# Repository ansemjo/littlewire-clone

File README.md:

# littlewire-clone

This is a clone of [Little Wire](https://littlewire.github.io/) by Ihsan Kehribar
with mostly SMD parts.

The special part about it is that it uses a female ICSP header soldered
on the edge of the board, which can be plugged into the target device
directly or used with "pogo-pin" adapters like
[the one by Pnoxi](https://www.tindie.com/products/pnoxi/avr-isp-pogo-pin-adapter-2x3-idc2x3-pogo-254mm/).

*Yes, I know my C2 is crooked .. Next time I'll use the "elongated pads" footprint.*

## Project structure

There's a number of interesting subdirectories, in order of applicability:

| Directory | Description |
| --------- | ----------- |
| [`hardware`](hardware/) | The KiCad 5.1.6 project with schematics and manufacturing files for PCB production. |
| [`bootloader`](bootloader/) | Instructions on how to put the `micronucleus` bootloader onto the chip once it's assembled. |
| [`firmware`](firmware/) | A vendored copy of the Little Wire / `usbtiny` source code to install the firmware.

## First batch

I have ordered the first batch thorugh [aisler.net](https://aisler.net/). From those
I have now assembled and tested two boards.

Currently I have **6** circuit boards left. Shoot me a
[message](https://twitter.com/ansemjo) if you want one of those.

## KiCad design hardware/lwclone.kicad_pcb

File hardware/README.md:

# Little Wire Clone

This directory describes a KiCad 5.1.6 project directory for my clone of
the Little Wire project by Ihsan Kehribar.

## Bill of Materials

Here is an informal BOM with the parts I used for my two boards so far.
Note that some of the values don't match with the schematic; I used some parts
that I had available from previous orders where it shouldn't make too much of
a difference anyway.

| ref | amount | partno | name |
| --- | ------ | ------ | ---- |
| U1 | 1 | ATTINY85-20PU | Microchip Technology ATTINY85-20PU IC MCU 8BIT 8KB FLASH 8DIP |
| USB1 | 1 | 10118194-0001LF | Amphenol ICC CONN RCPT USB2.0 MICRO B SMD R/A |
| C1, C2 | 2 | CL21B104KACNNNC | Samsung CAP CER 0.1UF 25V X7R 0805 |
| D1, D2 | 2 | MMSZ4684T1G | ON Semiconductor DIODE ZENER 3.3V 500MW SOD123 |
| D3 | 1 | LTST-C171AKT | Lite-On Inc. LED ORANGE CLEAR SMD |
| R1, R2 | 2 | RC0805FR-07100RL | Yageo RES SMD 100 OHM 1% 1/8W 0805 |
| R3 | 1 | RC0805FR-072K2L | Yageo RES SMD 2.2K OHM 1% 1/8W 0805 |
| R4 | 1 | RC0805FR-07330RL | Yageo RES SMD 330 OHM 1% 1/8W 0805 |
| ICSP1 | 1 | SSQ-103-01-T-D | Samtec Inc. CONN RCPT 6POS 0.1 TIN PCB |

## LICENSE

Copyright (c) 2020 Anton Semjonov

This source describes Open Hardware and is licensed under the CERN-OHL-P v2

You may redistribute and modify this documentation and make products using it
under the terms of the CERN-OHL-P v2 (https:/cern.ch/cern-ohl). This
documentation is distributed WITHOUT ANY EXPRESS OR IMPLIED WARRANTY, INCLUDING
OF MERCHANTABILITY, SATISFACTORY QUALITY AND FITNESS FOR A PARTICULAR PURPOSE.
Please see the CERN-OHL-P v2 for applicable conditions.

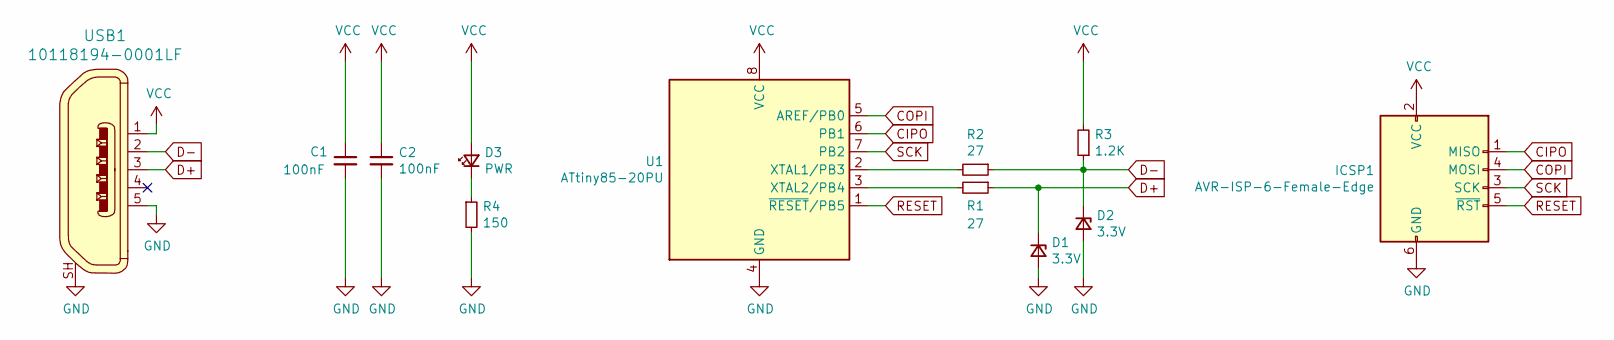
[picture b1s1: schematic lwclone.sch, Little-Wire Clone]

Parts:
C1, C2: 100nF; C_0805_2012Metric
D1, D2: 3.3V; D_SOD-123
D3: PWR; LED_0805_2012Metric
ICSP1: AVR-ISP-6-Female-Edge; IDC-Edge-Header-Female_2x03_P2.54mm
R1, R2: 27; R_0805_2012Metric
R3: 1.2K; R_0805_2012Metric
R4: 150; R_0805_2012Metric
U1: ATtiny85-20PU; DIP-8_W7.62mm
USB1: 10118194-0001LF; USB_Micro_B_Female_10118194-0001LF; MPN 10118194-0001LF; Digi-Key_PN 609-4618-1-ND

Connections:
CIPO: ICSP1.1 (MISO), U1.6 (PB1)
COPI: ICSP1.4 (MOSI), U1.5 (AREF/PB0)
D+: D1.1 (K), R1.1, USB1.3
D-: D2.1 (K), R2.1, R3.1, USB1.2
GND: C1.2, C2.2, D1.2 (A), D2.2 (A), ICSP1.6 (GND), R4.2, U1.4 (GND), USB1.5, USB1.SH
unnamed: D3.1 (K), R4.1
unnamed: R1.2, U1.3 (XTAL2/PB4)
unnamed: R2.2, U1.2 (XTAL1/PB3)
RESET: ICSP1.5 (~RST), U1.1 (~RESET~/PB5)
SCK: ICSP1.3 (SCK), U1.7 (PB2)
VCC: C1.1, C2.1, D3.2 (A), ICSP1.2 (VCC), R3.2, U1.8 (VCC), USB1.1

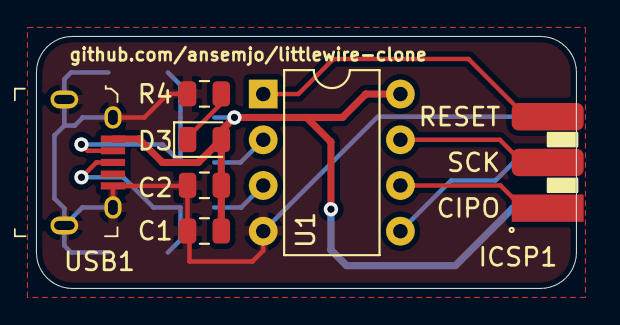
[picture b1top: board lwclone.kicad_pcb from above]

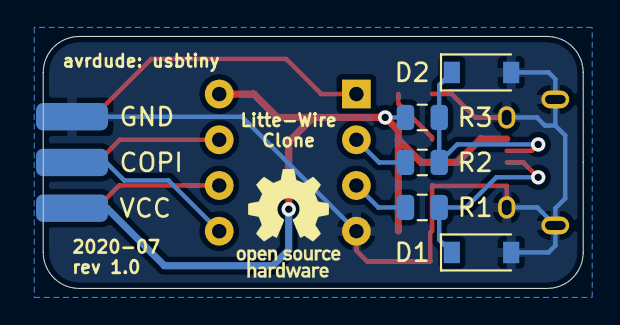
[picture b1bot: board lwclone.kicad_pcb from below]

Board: 2 copper layers, 30.0 x 14.0 mm, 12 parts (5 on the bottom side), 11 nets.

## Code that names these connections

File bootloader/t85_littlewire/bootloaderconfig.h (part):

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 * 
 * Controller type: ATtiny 85 - 16.5 MHz
 * Configuration:   Default configuration
 *       USB D- :   PB3
 *       USB D+ :   PB4
 *       Entry  :   Always
 *       LED    :   None
 *       OSCCAL :   Stays at 16 MHz
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 *                      external jumper. 
 *                      Adds 34 bytes.
 *
 *       JUMPER_PIN     Pin the jumper is connected to. (e.g. PB0)
 *       JUMPER_PORT    Port out register for the jumper (e.g. PORTB)  
 *       JUMPER_DDR     Port data direction register for the jumper (e.g. DDRB)  
 *       JUMPER_INP     Port inout register for the jumper (e.g. PINB)  
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
#define ENTRYMODE ENTRY_JUMPER

#define JUMPER_PIN    PB5
#define JUMPER_PORT   PORTB 
#define JUMPER_DDR    DDRB 
#define JUMPER_INP    PINB 
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
#define LED_DDR     DDRB
#define LED_PORT    PORTB
#define LED_PIN     PB1

/*
 *  This is the implementation of the LED code. Change the configuration above unless you want to 
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
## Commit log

2020-07-04 commit first revision ordered on aisler.net
2020-07-04 copy all used symbols to local lwclone.lib
2020-07-04 move files to hardware subdirectory
2020-07-04 add schematic pdf, pcb renders, first readme
2020-07-15 add pictures of arrived pcbs
2020-07-17 add micronucleus submodule
2020-07-17 add instructions in README on how to flash the bootloader
2020-07-17 vendor littlewire firmware from commit d918a4b with README
2020-07-17 amend release version note to firmware README
2020-07-17 update READMEs in root and hardware directories
2020-07-17 add a bill of materials table in hardware README
2020-07-17 fix images in hardware readme
2020-07-17 add CERN OHL-P v2 license in hardware/

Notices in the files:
bootloader/t85_littlewire/bootloaderconfig.h:
License: GNU GPL v2 (see License.txt
